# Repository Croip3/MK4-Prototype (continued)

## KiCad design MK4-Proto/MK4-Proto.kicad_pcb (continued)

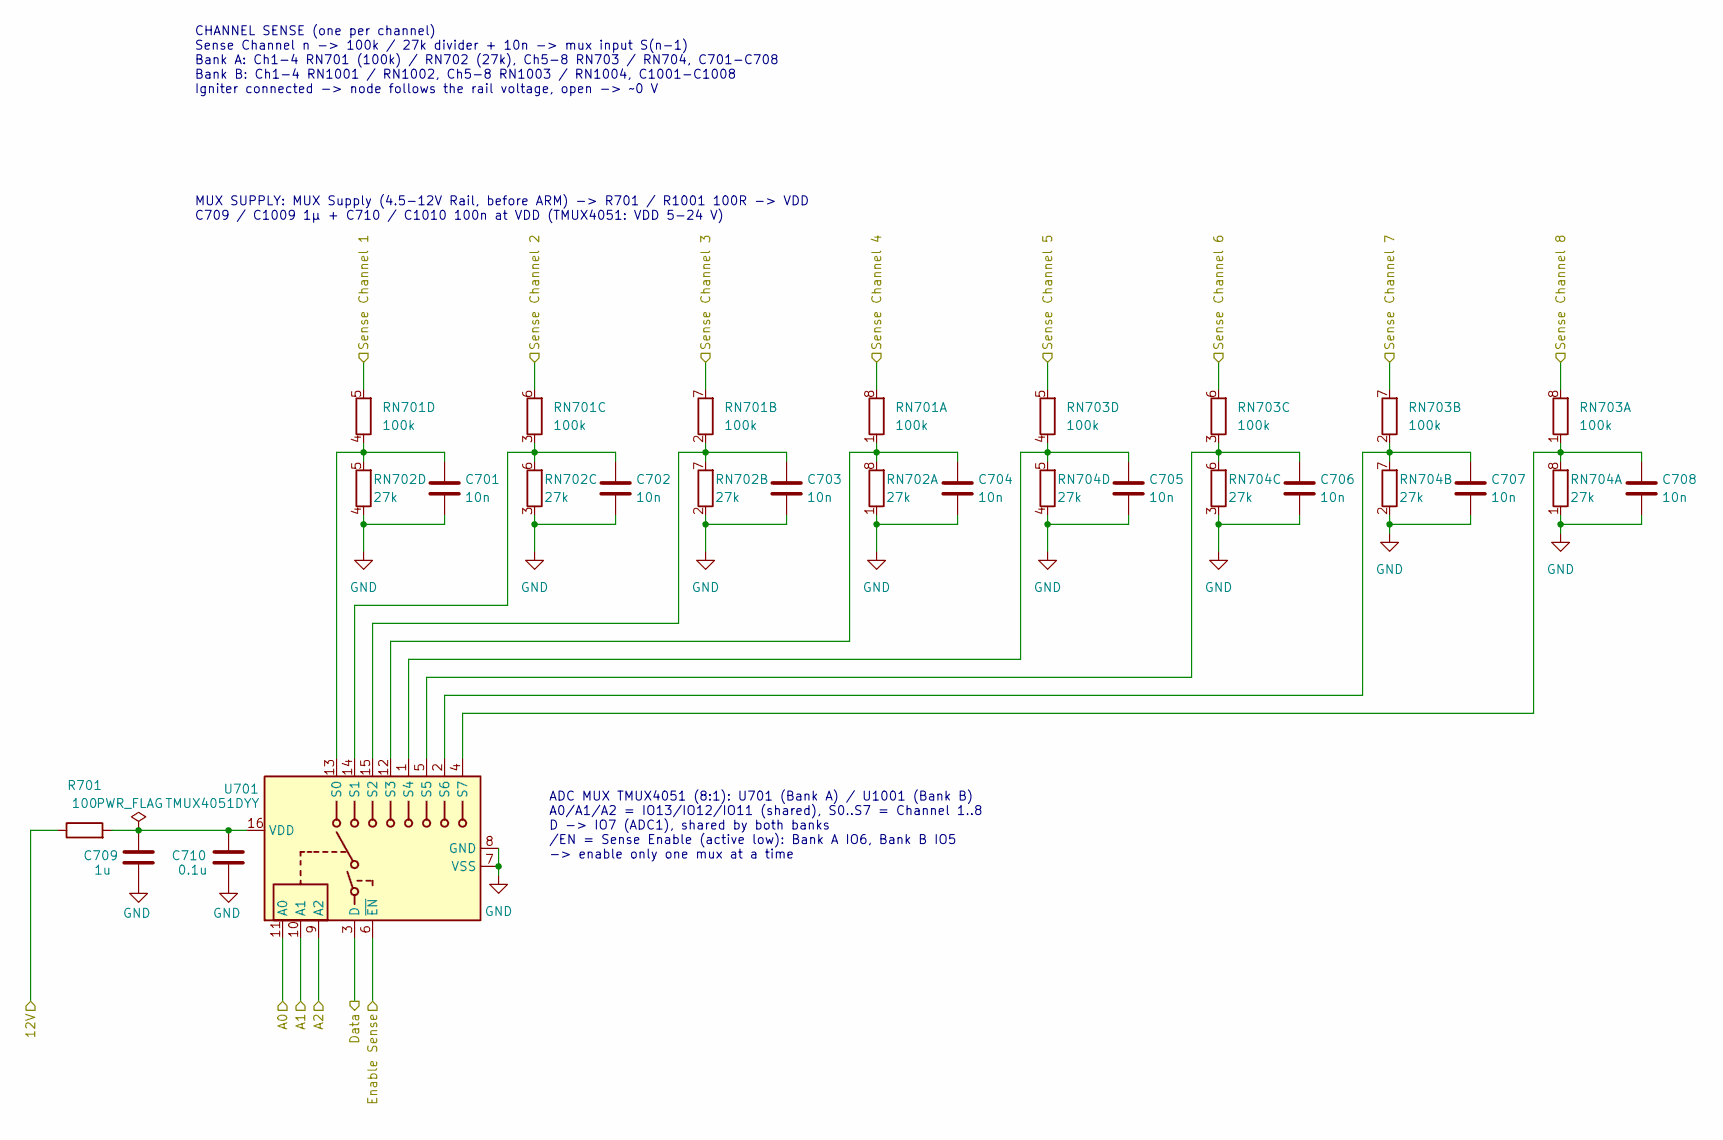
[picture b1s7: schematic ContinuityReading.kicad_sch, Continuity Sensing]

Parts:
C701, C702, C703, C704, C705, C706, C707, C708: 10n; C_0603_1608Metric; LCSC C57112
C709: 1u; C_0805_2012Metric_Pad1.18x1.45mm_HandSolder; LCSC C28323
C710: 0.1u; C_0805_2012Metric_Pad1.18x1.45mm_HandSolder; LCSC C49678
R701: 100; R_0603_1608Metric_Pad0.98x0.95mm_HandSolder; LCSC C22775
RN701, RN703: 100k; R_Array_Convex_4x0603; LCSC C1996
RN702, RN704: 27k; R_Array_Convex_4x0603; LCSC C25730
U701: TMUX4051DYY; Texas_DYY0016A_TSOT-23-16_2x4.2mm_P0.5mm; LCSC C22428440

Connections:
/ChannelBankA/A0: U701.11 (A0); also elsewhere on the board
/ChannelBankA/A1: U701.10 (A1); also elsewhere on the board
/ChannelBankA/A2: U701.9 (A2); also elsewhere on the board
/ChannelBankA/Channels/Continuity Sense 1: RN701.5 (R4.2); also elsewhere on the board
/ChannelBankA/Channels/Continuity Sense 2: RN701.6 (R3.2); also elsewhere on the board
/ChannelBankA/Channels/Continuity Sense 3: RN701.7 (R2.2); also elsewhere on the board
/ChannelBankA/Channels/Continuity Sense 4: RN701.8 (R1.2); also elsewhere on the board
/ChannelBankA/Channels/Continuity Sense 5: RN703.5 (R4.2); also elsewhere on the board
/ChannelBankA/Channels/Continuity Sense 6: RN703.6 (R3.2); also elsewhere on the board
/ChannelBankA/Channels/Continuity Sense 7: RN703.7 (R2.2); also elsewhere on the board
/ChannelBankA/Channels/Continuity Sense 8: RN703.8 (R1.2); also elsewhere on the board
/ChannelBankA/Data: U701.3 (D); also elsewhere on the board
/ChannelBankA/MUX Supply: R701.1; also elsewhere on the board
/ChannelBankA/Sense Enable: U701.6 (~EN); also elsewhere on the board
unnamed: C704.1, RN701.1 (R1.1), RN702.8 (R1.2), U701.12 (S3)
unnamed: C703.1, RN701.2 (R2.1), RN702.7 (R2.2), U701.15 (S2)
unnamed: C702.1, RN701.3 (R3.1), RN702.6 (R3.2), U701.14 (S1)
unnamed: C701.1, RN701.4 (R4.1), RN702.5 (R4.2), U701.13 (S0)
unnamed: C708.1, RN703.1 (R1.1), RN704.8 (R1.2), U701.4 (S7)
unnamed: C707.1, RN703.2 (R2.1), RN704.7 (R2.2), U701.2 (S6)
unnamed: C706.1, RN703.3 (R3.1), RN704.6 (R3.2), U701.5 (S5)
unnamed: C705.1, RN703.4 (R4.1), RN704.5 (R4.2), U701.1 (S4)
unnamed: C709.2, C710.2, R701.2, U701.16 (VDD)

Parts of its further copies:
C1001, C1002, C1003, C1004, C1005, C1006, C1007, C1008: 10n; C_0603_1608Metric; LCSC C57112
C1009: 1u; C_0805_2012Metric_Pad1.18x1.45mm_HandSolder; LCSC C28323
C1010: 0.1u; C_0805_2012Metric_Pad1.18x1.45mm_HandSolder; LCSC C49678
R1001: 100; R_0603_1608Metric_Pad0.98x0.95mm_HandSolder; LCSC C22775
RN1001, RN1003: 100k; R_Array_Convex_4x0603; LCSC C1996
RN1002, RN1004: 27k; R_Array_Convex_4x0603; LCSC C25730
U1001: TMUX4051DYY; Texas_DYY0016A_TSOT-23-16_2x4.2mm_P0.5mm; LCSC C22428440

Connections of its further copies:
/ChannelBankA/A0: U1001.11 (A0); also elsewhere on the board
/ChannelBankA/A1: U1001.10 (A1); also elsewhere on the board
/ChannelBankA/A2: U1001.9 (A2); also elsewhere on the board
/ChannelBankA/Data: U1001.3 (D); also elsewhere on the board
/ChannelBankA/MUX Supply: R1001.1; also elsewhere on the board
/ChannelBankB/Channels/Continuity Sense 1: RN1001.5 (R4.2); also elsewhere on the board
/ChannelBankB/Channels/Continuity Sense 2: RN1001.6 (R3.2); also elsewhere on the board
/ChannelBankB/Channels/Continuity Sense 3: RN1001.7 (R2.2); also elsewhere on the board
/ChannelBankB/Channels/Continuity Sense 4: RN1001.8 (R1.2); also elsewhere on the board
/ChannelBankB/Channels/Continuity Sense 5: RN1003.5 (R4.2); also elsewhere on the board
/ChannelBankB/Channels/Continuity Sense 6: RN1003.6 (R3.2); also elsewhere on the board
/ChannelBankB/Channels/Continuity Sense 7: RN1003.7 (R2.2); also elsewhere on the board
/ChannelBankB/Channels/Continuity Sense 8: RN1003.8 (R1.2); also elsewhere on the board
/ChannelBankB/Sense Enable: U1001.6 (~EN); also elsewhere on the board
unnamed: C1004.1, RN1001.1 (R1.1), RN1002.8 (R1.2), U1001.12 (S3)
unnamed: C1003.1, RN1001.2 (R2.1), RN1002.7 (R2.2), U1001.15 (S2)
unnamed: C1002.1, RN1001.3 (R3.1), RN1002.6 (R3.2), U1001.14 (S1)
unnamed: C1001.1, RN1001.4 (R4.1), RN1002.5 (R4.2), U1001.13 (S0)
unnamed: C1008.1, RN1003.1 (R1.1), RN1004.8 (R1.2), U1001.4 (S7)
unnamed: C1007.1, RN1003.2 (R2.1), RN1004.7 (R2.2), U1001.2 (S6)
unnamed: C1006.1, RN1003.3 (R3.1), RN1004.6 (R3.2), U1001.5 (S5)
unnamed: C1005.1, RN1003.4 (R4.1), RN1004.5 (R4.2), U1001.1 (S4)
unnamed: C1009.2, C1010.2, R1001.2, U1001.16 (VDD)

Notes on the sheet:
MUX SUPPLY: MUX Supply (4.5-12V Rail, before ARM) -> R701 / R1001 100R -> VDD C709 / C1009 1µ + C710 / C1010 100n at VDD (TMUX4051: VDD 5-24 V)
ADC MUX TMUX4051 (8:1): U701 (Bank A) / U1001 (Bank B) A0/A1/A2 = IO13/IO12/IO11 (shared), S0..S7 = Channel 1..8 D -> IO7 (ADC1), shared by both banks /EN = Sense Enable (active low): Bank A IO6, Bank B IO5 -> enable only one mux at a time
CHANNEL SENSE (one per channel) Sense Channel n -> 100k / 27k divider + 10n -> mux input S(n-1) Bank A: Ch1-4 RN701 (100k) / RN702 (27k), Ch5-8 RN703 / RN704, C701-C708 Bank B: Ch1-4 RN1001 / RN1002, Ch5-8 RN1003 / RN1004, C1001-C1008 Igniter connected -> node follows the rail voltage, open -> ~0 V

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
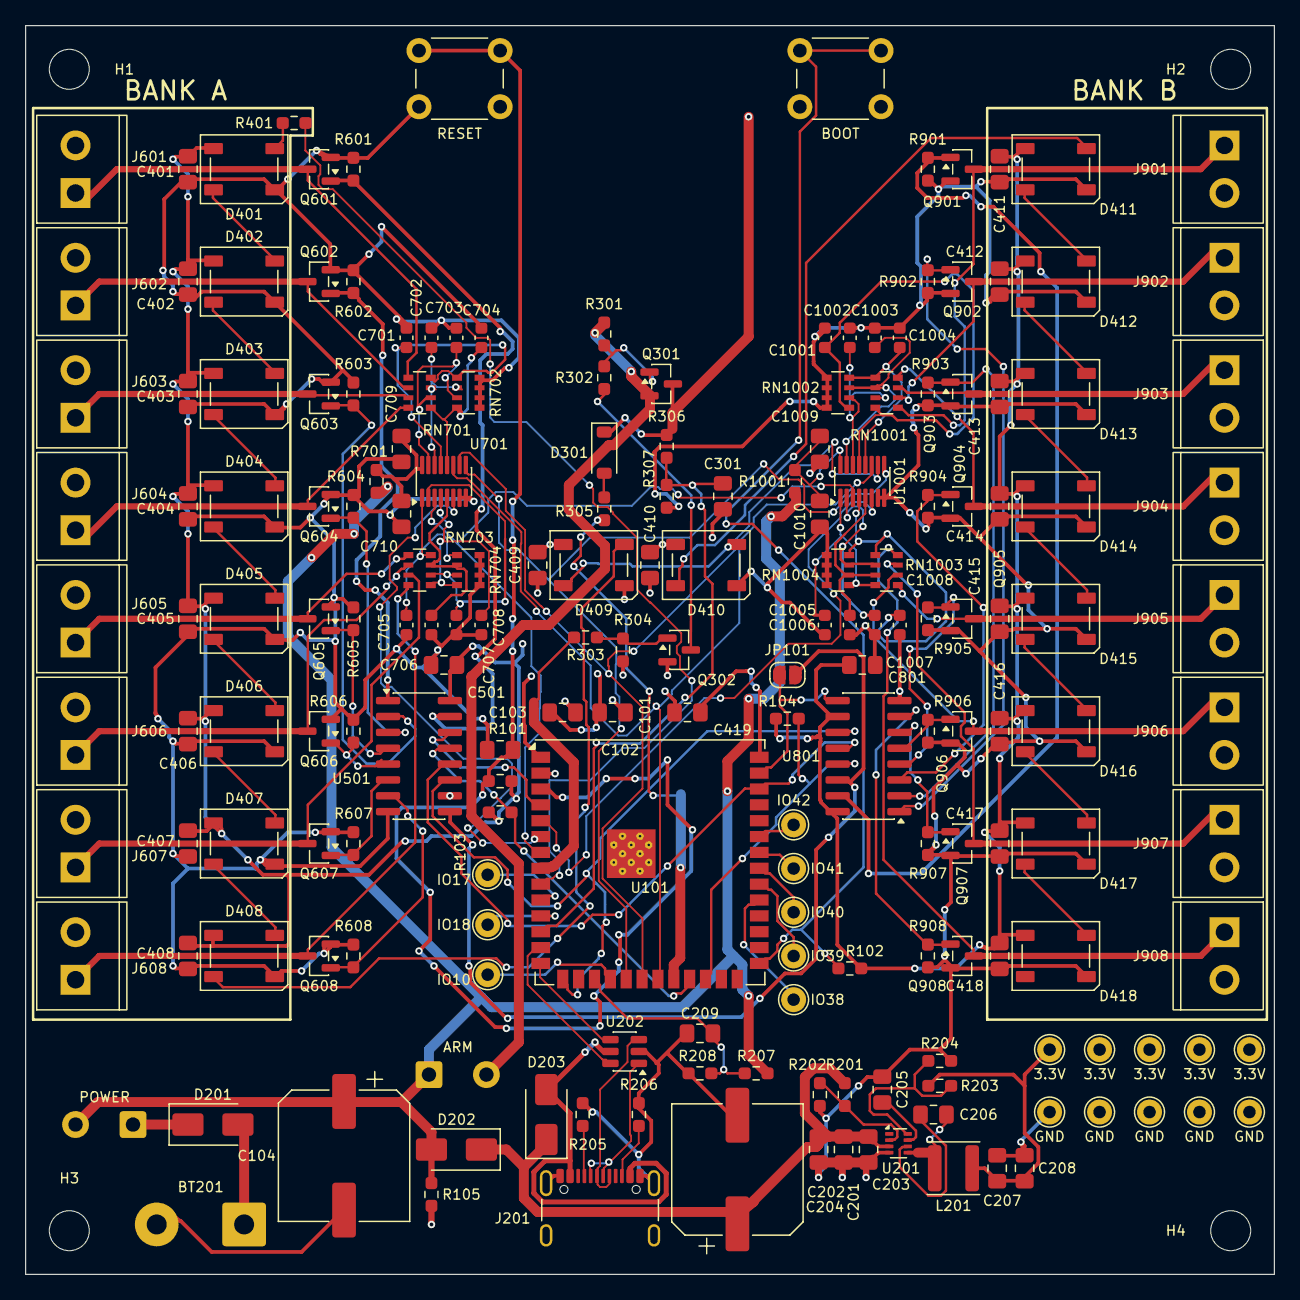
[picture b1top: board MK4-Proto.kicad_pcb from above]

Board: 4 copper layers, 100.0 x 100.0 mm, 196 parts (1 on the bottom side), 120 nets.

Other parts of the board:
C501: 0.1u; C_0805_2012Metric_Pad1.18x1.45mm_HandSolder
H1, H2, H3, H4: MountingHole_3.2mm_M3
LOGO1: Logo_Longarm
U501: 74HC595; SOIC-16_3.9x9.9mm_P1.27mm

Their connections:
/ChannelBankA/Channel Enable: U501.13 (~OE); also elsewhere on the board
/ChannelBankA/Channels/Channel 1: U501.15 (QA); also elsewhere on the board
/ChannelBankA/Channels/Channel 2: U501.1 (QB); also elsewhere on the board
/ChannelBankA/Channels/Channel 3: U501.2 (QC); also elsewhere on the board
/ChannelBankA/Channels/Channel 4: U501.3 (QD); also elsewhere on the board
/ChannelBankA/Channels/Channel 5: U501.4 (QE); also elsewhere on the board
/ChannelBankA/Channels/Channel 6: U501.5 (QF); also elsewhere on the board
/ChannelBankA/Channels/Channel 7: U501.6 (QG); also elsewhere on the board
/ChannelBankA/Channels/Channel 8: U501.7 (QH); also elsewhere on the board
/ChannelBankA/RCLK: U501.12 (RCLK); also elsewhere on the board
/ChannelBankA/SER: U501.14 (SER); also elsewhere on the board
/ChannelBankA/SRCLK: U501.11 (SRCLK); also elsewhere on the board
/ChannelBankA/Shift Register Chain: U501.9 (QH'); also elsewhere on the board
